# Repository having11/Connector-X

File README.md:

# Connector-X

A drop-in, highly-configurable IO board compatible with the NI/FRC RoboRIO

- [Connector-X](#connector-x)
  - [The concept](#the-concept)
  - [Hardware features](#hardware-features)
  - [Attaching to your RIO](#attaching-to-your-rio)
  - [What are ports and zones?](#what-are-ports-and-zones)
  - [It can show images](#it-can-show-images)
  - [Command structure](#command-structure)
  - [Test sequences](#test-sequences)
  - [Expansion](#expansion)

## The concept

Have you ever wanted to leverage the power and extensibility of the Arduino ecosystem on other hardware but realized it's not supported? This was the case for FRC team 5690 SubZero Robotics in the 2023 season when we were attempting to add sensors and LEDs to our robot. Born from this struggle was a very simple Arduino Nano-based board that supported a single LED strip, limited LED patterns, and a duty-cycle output for lidar. As one might imagine, this was quite limited, so the 2023 off-season was spent designing and then redesigning a brand new system called the Connector-X (Connect Anything).

The new system is meant to be far faster and more flexible, as its Raspberry Pi Pico processor allows it to act as both a peripheral for a RoboRIO and a central device for connecting sensors.

## Hardware features

Starting along the top of the Connector-X is a pair of buttons that allow for reconfiguring the device and resetting it if needed. The DIP switch to the right was used to set the I2C address, but recent changes to the firmware have made it unnecessary. Lastly, the 3.3V regulator and Schottky diode help regulate incoming power and prevent damage if the inputs are accidentally reversed.

The DC barrel jack is meant for connecting 5V, center-positive power from a buck converter or other source that can supply a sufficient amount of current (> 5A preferred). Two LED ports sit below it, and each one has a starting, test WS2812B LED to help debug LED strip problems. The center has headers for 1 x SPI, 2 x I2C, and 3 x GPIO. Status indicators below the Pico display Power, Pico functionality, and I2C activity.

## Attaching to your RIO

At the bottom of the board is a male 2 x 17 header and a female 2 x 17 header, both of which conform to and pass-through the RIO's MXP connector standard. The Connector-X itself is only electrically connected to the I2C `SDA`, I2C `SCL`, and `GND` pins, meaning that a power issue on the board will not affect the RIO.

## What are ports and zones?

As mentioned before, the two ports each connect to a single LED strip, but that leads to the question of how different patterns can be easily shown on the same strip. So rather than connecting a strip per-port, the Connector-X allows for the strip to be subdivided into virtual zones that range from a single pixel all the way to the entire strip's length. To specify one, simply declare the offset (inclusive) and the size of the zone while ensuring it stays within the total number of LEDs present in the strip. The controlling device then sends commands to select the desired port and zone by index when setting colors/patterns.

## It can show images

Within the `Configuration`, either a `strip` or `matrix` configuration can be set. In the case of a `matrix`, the port is automatically split into two zones with the first being the single test LED and the second as the matrix itself. Currently, there are seven patterns that make use of the matrix, and they generally work by accessing images as follows:

1. A folder is created within the [data](./connector_x/data/) directory
2. 16-bit RGB bitmaps are placed into the folder. Names should be numeric, start at 0, and have the exact same number of images as the number of states specified in the [Pattern configuration](./connector_x/include/Patterns.h)
3. Selecting the pattern from a controlling device causes the Connector-X to cycle through them with the delay specified in the config or the command

## Command structure

Now that Commands have been mentioned several times, you're probably wondering what it actually _is_. A Command is simply a small amount of data that the controlling device sends to the Connector-X containing the `CommandType` and an arbitrary amount of additional data depending on what the `CommandType` equals.

| `CommandType`                   |                              Description                              |         Additional data          |
| :------------------------------ | :-------------------------------------------------------------------: | :------------------------------: |
| On                              |                         Turns on an LED port                          |               N/A                |
| Off                             |                         Turns off an LED port                         |               N/A                |
| Pattern                         |                  Sets the current Pattern for a Zone                  | Pattern type, is one-shot, delay |
| ChangeColor                     |                   Sets the current Color for a Zone                   |             R, G, B              |
| ReadPatternDone                 |               Checks if the set Pattern is done running               |               N/A                |
| SetLedPort                      |                       Sets the active LED Port                        |           Port number            |
| DigitalSetup                    |          Sets the mode (Read or Write) for a Digital IO Port          |        Port number, mode         |
| DigitalWrite                    |                  Sets a Digital IO Port High or Low                   |        Port number, value        |
| DigitalRead                     |                    Reads a Digital IO Port's state                    |           Port number            |
| SetConfig (unused)              |                 Sets a new Config for the Connector-X                 |               N/A                |
| RadioSend (unused)              |  Sends data to other teams via the onboard Packet Radio when enabled  |               N/A                |
| RadioGetLatestReceived (unused) |            Gets the latest Packet Radio data when enabled             |               N/A                |
| GetColor                        |                   Gets the active Color for a Zone                    |               N/A                |
| GetPort                         |                        Gets the selected Port                         |               N/A                |
| SetPatternZone                  |              Sets the current Zone for the current Port               |     Zone index, is reversed      |
| SetNewZones (unused)            |               Configures new Zones for the current Port               |      Zone count, zone array      |
| SyncStates                      | Sets the selected Zones' Patterns to the same State (animation frame) |   Zone count, zone index array   |

## Test sequences

It is possible to execute a series of commands upon startup without intervention from the controlling device. To do so, simply specify a list of `TestCommand`s in [`TestCommands.h`](./connector_x/include/TestCommands.h) that include the command type and any other required `commandData` within the `union`.

## Expansion

Feel free to add Commands and Patterns to expand the functionality of your Connector-X. Some ideas might include adding an I2C sensor and passing it through, controlling an LED, or displaying images on a screen via SPI.

V3 coming soon...

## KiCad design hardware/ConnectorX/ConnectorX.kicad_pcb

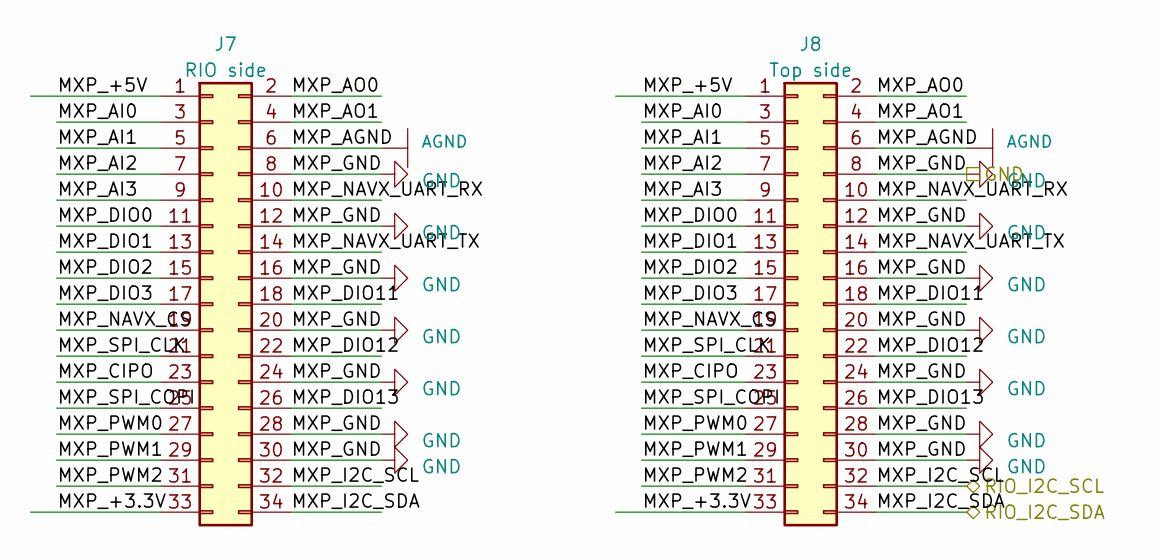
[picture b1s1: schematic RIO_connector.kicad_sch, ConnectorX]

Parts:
J7: RIO side; PinSocket_2x17_P2.54mm_Vertical
J8: Top side; PinHeader_2x17_P2.54mm_Vertical

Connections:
/I2C0_SCL: J7.32, J8.32; also elsewhere on the board
/MCU/I2C0_SDA: J7.34, J8.34; also elsewhere on the board
/RIO_connector/MXP_+3.3V: J7.33, J8.33
/RIO_connector/MXP_+5V: J7.1, J8.1
/RIO_connector/MXP_AI0: J7.3, J8.3
/RIO_connector/MXP_AI1: J7.5, J8.5
/RIO_connector/MXP_AI2: J7.7, J8.7
/RIO_connector/MXP_AI3: J7.9, J8.9
/RIO_connector/MXP_AO0: J7.2, J8.2
/RIO_connector/MXP_AO1: J7.4, J8.4
/RIO_connector/MXP_CIPO: J7.23, J8.23
/RIO_connector/MXP_DIO0: J7.11, J8.11
/RIO_connector/MXP_DIO1: J7.13, J8.13
/RIO_connector/MXP_DIO2: J7.15, J8.15
/RIO_connector/MXP_DIO3: J7.17, J8.17
/RIO_connector/MXP_DIO11: J7.18, J8.18
/RIO_connector/MXP_DIO12: J7.22, J8.22
/RIO_connector/MXP_DIO13: J7.26, J8.26
/RIO_connector/MXP_NAVX_CS: J7.19, J8.19
/RIO_connector/MXP_NAVX_UART_RX: J7.10, J8.10
/RIO_connector/MXP_NAVX_UART_TX: J7.14, J8.14
/RIO_connector/MXP_PWM0: J7.27, J8.27
/RIO_connector/MXP_PWM1: J7.29, J8.29
/RIO_connector/MXP_PWM2: J7.31, J8.31
/RIO_connector/MXP_SPI_CLK: J7.21, J8.21
/RIO_connector/MXP_SPI_COPI: J7.25, J8.25
AGND: J7.6, J8.6
GND: J7.8, J7.12, J7.16, J7.20, J7.24, J7.28, J7.30, J8.8, J8.12, J8.16, J8.20, J8.24, J8.28, J8.30; also elsewhere on the board

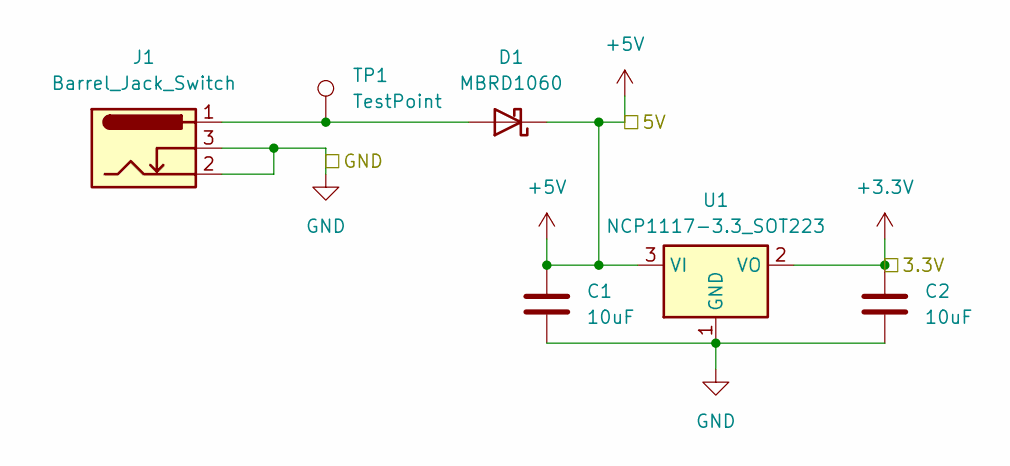
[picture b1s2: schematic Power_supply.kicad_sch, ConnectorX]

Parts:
C1, C2: 10uF; C_0603_1608Metric
D1: MBRD1060; TO-252-2
J1: Barrel_Jack_Switch; BarrelJack_Horizontal
TP1: TestPoint; TestPoint_Pad_D2.5mm
U1: NCP1117-3.3_SOT223; SOT-223-3_TabPin2

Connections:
+3.3V: C2.1, U1.2 (VO); also elsewhere on the board
+5V: C1.1, D1.1 (K), U1.3 (VI); also elsewhere on the board
GND: C1.2, C2.2, J1.2, J1.3, U1.1 (GND); also elsewhere on the board
unnamed: D1.2 (A), J1.1, TP1.1

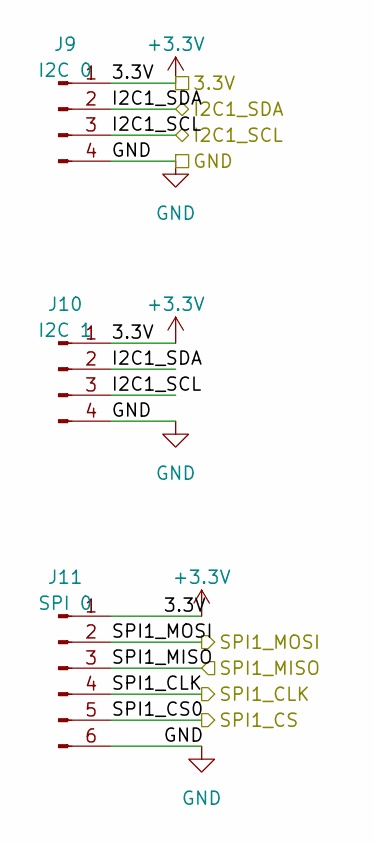
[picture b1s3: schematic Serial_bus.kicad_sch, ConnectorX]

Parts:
J9: I2C 0; PinHeader_1x04_P2.54mm_Vertical
J10: I2C 1; PinHeader_1x04_P2.54mm_Vertical
J11: SPI 0; PinHeader_1x06_P2.54mm_Vertical

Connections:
+3.3V: J9.1, J10.1, J11.1; also elsewhere on the board
/MCU/I2C1_SCL: J9.3, J10.3; also elsewhere on the board
/MCU/I2C1_SDA: J9.2, J10.2; also elsewhere on the board
/MCU/SPI1_CLK: J11.4; also elsewhere on the board
/MCU/SPI1_CS: J11.5; also elsewhere on the board
/MCU/SPI1_MISO: J11.3; also elsewhere on the board
/MCU/SPI1_MOSI: J11.2; also elsewhere on the board
GND: J9.4, J10.4, J11.6; also elsewhere on the board

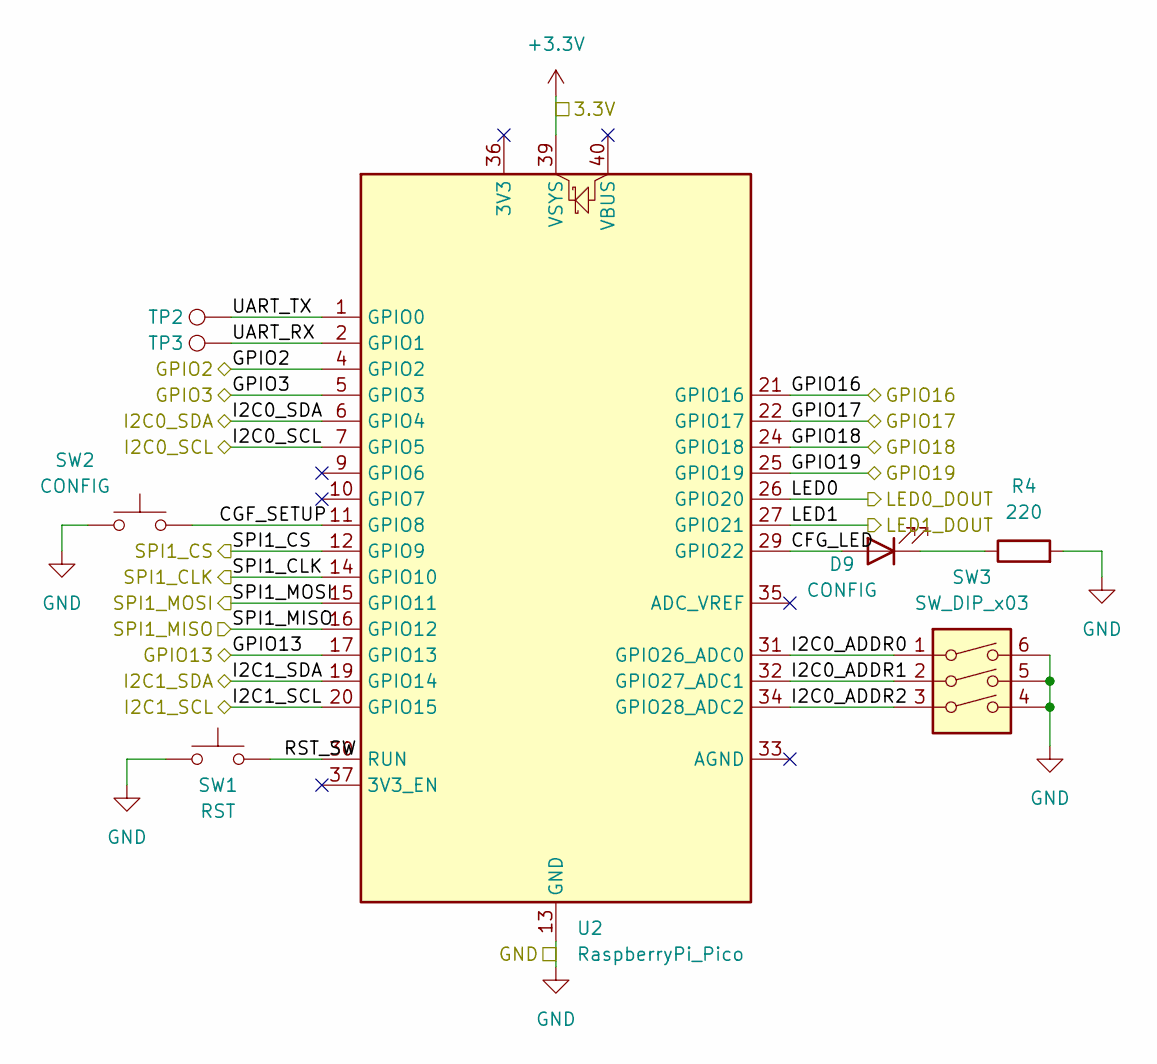
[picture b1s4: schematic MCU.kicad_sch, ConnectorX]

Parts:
D9: CONFIG; LED_0805_2012Metric
R4: 220; R_0603_1608Metric
SW1: RST; SW_SPST_PTS645
SW2: CONFIG; SW_SPST_PTS645
SW3: SW_DIP_x03; SW_DIP_SPSTx03_Slide_6.7x9.18mm_W6.73mm_P2.54mm_LowProfile_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
TP2, TP3: TestPoint; TestPoint_Pad_D2.5mm
U2: RaspberryPi_Pico; RaspberryPi_Pico_Common

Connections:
+3.3V: U2.39 (VSYS); also elsewhere on the board
/I2C0_SCL: U2.7 (GPIO5); also elsewhere on the board
/MCU/CFG_LED: D9.2 (A), U2.29 (GPIO22)
/MCU/CGF_SETUP: SW2.2, U2.11 (GPIO8)
/MCU/GPIO2: U2.4 (GPIO2); also elsewhere on the board
/MCU/GPIO3: U2.5 (GPIO3); also elsewhere on the board
/MCU/GPIO13: U2.17 (GPIO13)
/MCU/GPIO16: U2.21 (GPIO16); also elsewhere on the board
/MCU/GPIO17: U2.22 (GPIO17)
/MCU/GPIO18: U2.24 (GPIO18)
/MCU/I2C0_ADDR0: SW3.1, U2.31 (GPIO26_ADC0)
/MCU/I2C0_ADDR1: SW3.2, U2.32 (GPIO27_ADC1)
/MCU/I2C0_ADDR2: SW3.3, U2.34 (GPIO28_ADC2)
/MCU/I2C0_SDA: U2.6 (GPIO4); also elsewhere on the board
/MCU/I2C1_SCL: U2.20 (GPIO15); also elsewhere on the board
/MCU/I2C1_SDA: U2.19 (GPIO14); also elsewhere on the board
/MCU/LED0: U2.26 (GPIO20); also elsewhere on the board
/MCU/LED1: U2.27 (GPIO21); also elsewhere on the board
/MCU/RST_SW: SW1.2, U2.30 (RUN)
/MCU/SPI1_CLK: U2.14 (GPIO10); also elsewhere on the board
/MCU/SPI1_CS: U2.12 (GPIO9); also elsewhere on the board
/MCU/SPI1_MISO: U2.16 (GPIO12); also elsewhere on the board
/MCU/SPI1_MOSI: U2.15 (GPIO11); also elsewhere on the board
/MCU/UART_RX: TP3.1, U2.2 (GPIO1)
/MCU/UART_TX: TP2.1, U2.1 (GPIO0)
/PICO_ALV: U2.25 (GPIO19); also elsewhere on the board
GND: R4.2, SW1.1, SW2.1, SW3.4, SW3.5, SW3.6, U2.3 (GND), U2.8 (GND), U2.13 (GND), U2.18 (GND), U2.23 (GND), U2.28 (GND), U2.38 (GND); also elsewhere on the board
unnamed: D9.1 (K), R4.1

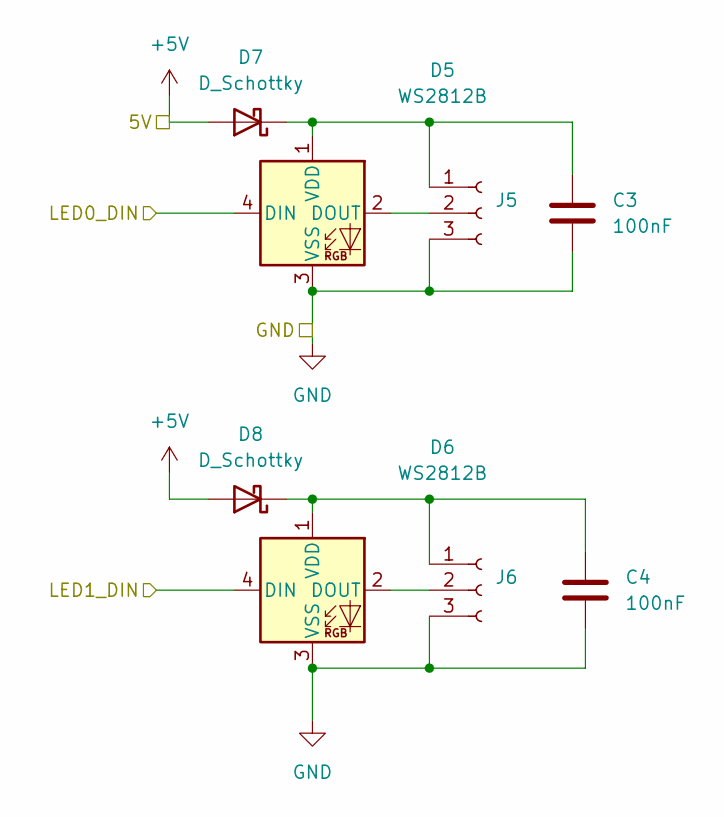
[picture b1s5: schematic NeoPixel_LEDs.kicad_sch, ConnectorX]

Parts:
C3, C4: 100nF; C_0603_1608Metric
D5, D6: WS2812B; LED_WS2812B_PLCC4_5.0x5.0mm_P3.2mm
D7, D8: D_Schottky; D_SMA
J5, J6: Conn_01x03_Socket; JST_VH_B3PS-VH_1x03_P3.96mm_Horizontal

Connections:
+5V: D7.2 (A), D8.2 (A); also elsewhere on the board
/MCU/LED0: D5.4 (DIN); also elsewhere on the board
/MCU/LED1: D6.4 (DIN); also elsewhere on the board
GND: C3.2, C4.2, D5.3 (VSS), D6.3 (VSS), J5.3, J6.3; also elsewhere on the board
unnamed: D5.2 (DOUT), J5.2
unnamed: C3.1, D5.1 (VDD), D7.1 (K), J5.1
unnamed: D6.2 (DOUT), J6.2
unnamed: C4.1, D6.1 (VDD), D8.1 (K), J6.1

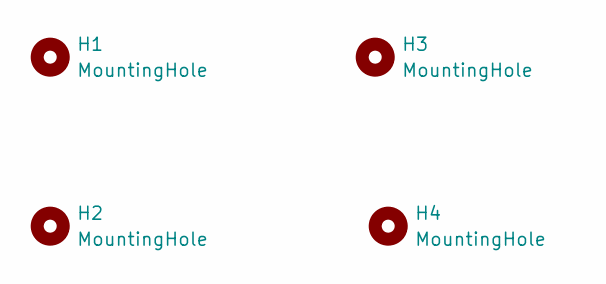
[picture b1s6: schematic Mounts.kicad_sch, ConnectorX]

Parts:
H1, H2, H3, H4: MountingHole; MountingHole_3.2mm_M3_Pad_Via

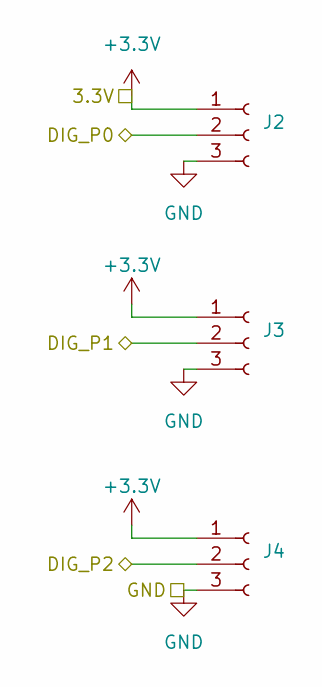
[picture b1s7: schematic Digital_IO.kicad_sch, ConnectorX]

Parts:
J2, J3, J4: Conn_01x03_Socket; PinHeader_1x03_P2.54mm_Horizontal

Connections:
+3.3V: J2.1, J3.1, J4.1; also elsewhere on the board
/MCU/GPIO2: J2.2; also elsewhere on the board
/MCU/GPIO3: J3.2; also elsewhere on the board
/MCU/GPIO16: J4.2; also elsewhere on the board
GND: J2.3, J3.3, J4.3; also elsewhere on the board

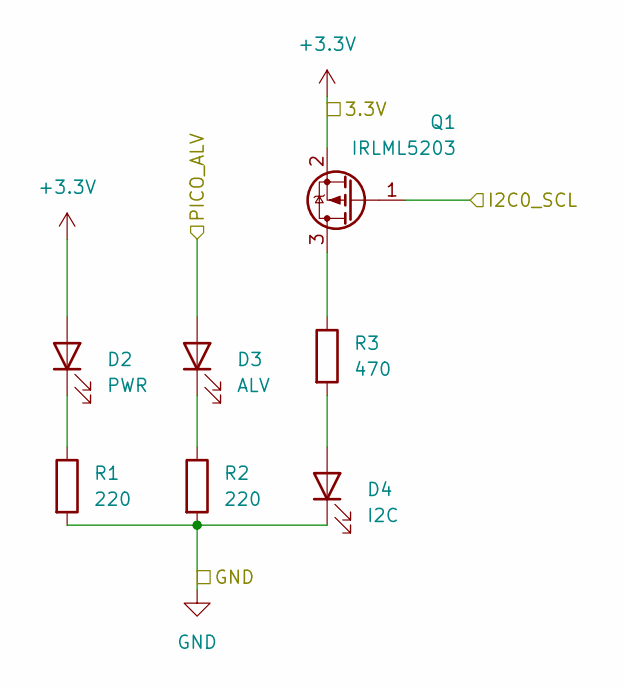
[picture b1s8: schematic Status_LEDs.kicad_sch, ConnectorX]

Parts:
D2: PWR; LED_1206_3216Metric
D3: ALV; LED_1206_3216Metric
D4: I2C; LED_1206_3216Metric
Q1: IRLML5203; SOT-23
R1, R2: 220; R_0603_1608Metric
R3: 470; R_0603_1608Metric

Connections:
+3.3V: D2.2 (A), Q1.2 (S); also elsewhere on the board
/I2C0_SCL: Q1.1 (G); also elsewhere on the board
/PICO_ALV: D3.2 (A); also elsewhere on the board
GND: D4.1 (K), R1.2, R2.2; also elsewhere on the board
unnamed: D2.1 (K), R1.1
unnamed: D3.1 (K), R2.1
unnamed: D4.2 (A), R3.2
unnamed: Q1.3 (D), R3.1

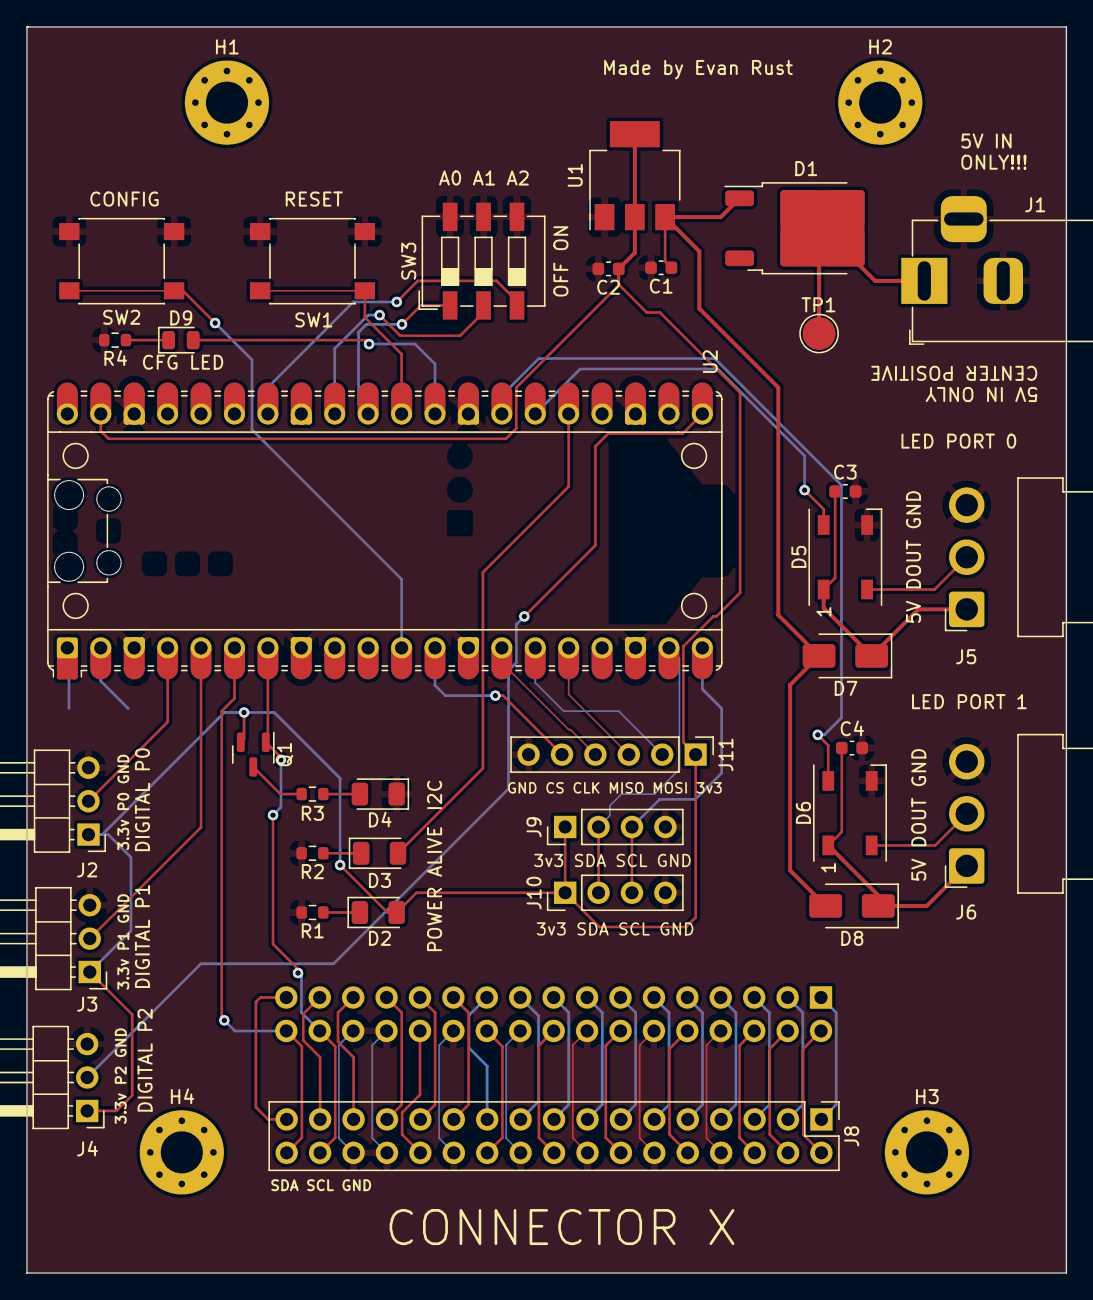
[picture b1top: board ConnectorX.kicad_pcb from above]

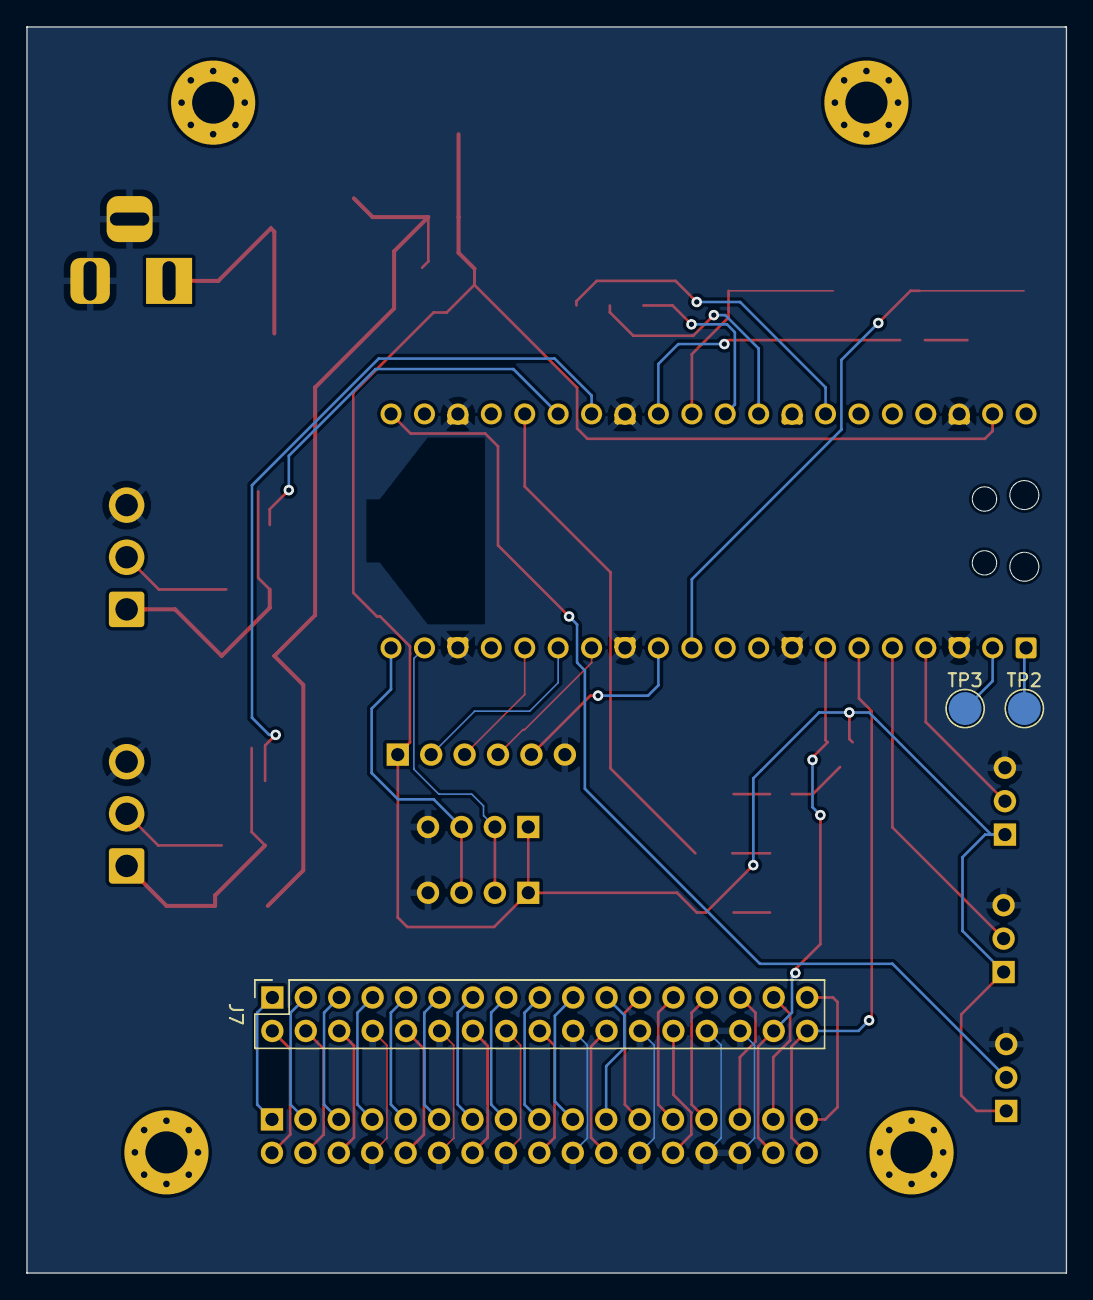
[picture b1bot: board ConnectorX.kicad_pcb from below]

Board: 2 copper layers, 79.0 x 94.7 mm, 41 parts (3 on the bottom side), 60 nets.

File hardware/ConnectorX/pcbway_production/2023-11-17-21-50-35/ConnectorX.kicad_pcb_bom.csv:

designator,quantity,value,pack,mpn,mount_type
"C1, C2",2,10uF,C_0603_1608Metric,,smt
"C3, C4",2,100nF,C_0603_1608Metric,,smt
D1,1,MBRD1060,TO-252-2,,smt
D2,1,PWR,LED_1206_3216Metric,,smt
D3,1,ALV,LED_1206_3216Metric,,smt
D4,1,I2C,LED_1206_3216Metric,,smt
"D5, D6",2,WS2812B,LED_WS2812B_PLCC4_5.0x5.0mm_P3.2mm,,smt
"D7, D8",2,D_Schottky,D_SMA,,smt
D9,1,CONFIG,LED_0805_2012Metric,,smt
"H1, H2, H3, H4",4,MountingHole,MountingHole_3.2mm_M3_Pad_Via,,tht
J1,1,Barrel_Jack_Switch,BarrelJack_Horizontal,,tht
J10,1,I2C 1,PinHeader_1x04_P2.54mm_Vertical,,tht
J11,1,SPI 0,PinHeader_1x06_P2.54mm_Vertical,,tht
"J2, J3, J4",3,Conn_01x03_Socket,PinHeader_1x03_P2.54mm_Horizontal,,tht
"J5, J6",2,Conn_01x03_Socket,JST_VH_B3PS-VH_1x03_P3.96mm_Horizontal,,tht
J7,1,RIO side,PinSocket_2x17_P2.54mm_Vertical,,tht
J8,1,Top side,PinHeader_2x17_P2.54mm_Vertical,,tht
J9,1,I2C 0,PinHeader_1x04_P2.54mm_Vertical,,tht
Q1,1,IRLML5203TRPBF,SOT-23,,smt
"R1, R2, R4",3,220,R_0603_1608Metric,,smt
R3,1,470,R_0603_1608Metric,,smt
SW1,1,RST,SW_SPST_PTS645,,smt
SW2,1,CONFIG,SW_SPST_PTS645,,smt
SW3,1,SW_DIP_x03,SW_DIP_SPSTx03_Slide_6.7x9.18mm_W6.73mm_P2.54mm_LowProfile_JPin,,smt
"TP1, TP2, TP3",3,TestPoint,TestPoint_Pad_D2.5mm,,tht
U1,1,NCP1117-3.3_SOT223,SOT-223-3_TabPin2,,smt
U2,1,RaspberryPi_Pico,RaspberryPi_Pico_Common,,tht

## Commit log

2023-11-24 Initial upload
2023-11-24 Initial upload (#1)
2023-11-30 Tested on hardware
2023-12-26 get current color
2023-12-26 array fixes
2023-12-26 remove un-needed mutex
2023-12-26 add handler in centralRespond()
2023-12-26 get port
2023-12-27 create structs for GetColor and GetPort
2024-01-13 Add CommandParser
2024-01-13 Fix led 0 count prompt
2024-01-13 assign ledPort directly to res.responseData.responseReadPort.msg
2024-01-13 get current color (#2)
    * get current color
    * array fixes
    * remove un-needed mutex
    * add handler in centralRespond()
    * get port
    * add handler in centralRespond()
2024-01-13 make compile
2024-01-14 Properly join bus as slave
2024-01-14 comment out print
2024-01-19 Fix rapid commands
2024-01-21 start zones
2024-01-21 min working
2024-01-21 multizone
2024-01-21 It works!
2024-01-21 add set zones command (untested)
2024-01-22 fully working
2024-01-22 add chase and sine patterns working
2024-01-23 finalize zone updates
2024-01-25 add core idling
2024-01-27 Pattern Zones (#3)
    * start zones
    * min working
    * multizone
    * It works!
    * add set zones command (untested)
    * fully working
2024-02-04 fix display
2024-02-04 update for all zones
2024-02-18 Only show LEDs when needed
2024-02-18 Expand Core1 stack size
2024-02-19 4 zones by default
2024-02-24 async commands
2024-02-24 more fixes
2024-02-25 set port
2024-02-29 hard-coded
2024-02-29 hard-code address
2024-03-09 read and show bitmaps
2024-03-09 add images
2024-03-09 make configuration header-based
2024-03-10 show bitmaps
2024-03-10 fix frame count
2024-03-11 extend test pattern
2024-03-16 add amogus
2024-03-16 update zones
2024-03-20 Add FFT
2024-04-06 owo pattern
2024-04-06 use mpr121
2024-04-17 add owo flag
2024-04-30 test third zone
2024-05-01 update config
2024-05-01 Pattern Zones (#4)
    * start zones
    * min working
    * multizone
    * It works!
    * add set zones command (untested)
    * fully working
2024-05-07 Initial documentation
2024-05-07 Images and commands
2024-05-07 grammar
2024-05-07 typo
2024-05-07 V2 Documentation (#5)
    * Initial documentation
    * Images and commands
    * grammar
    * typo
